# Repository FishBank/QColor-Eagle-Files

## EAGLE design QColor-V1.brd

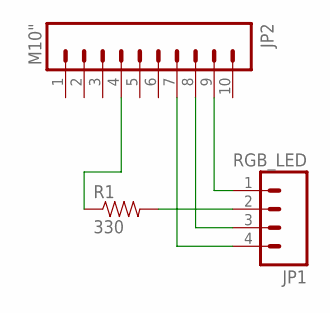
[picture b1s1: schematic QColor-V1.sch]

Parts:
JP1: RGB_LED; 1X04
JP2: M10"; 1X10
R1: 330; AXIAL-0.3

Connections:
unnamed: JP2.4, R1.P$1 (1)
unnamed: JP1.2, R1.P$2 (2)
unnamed: JP1.1, JP2.9
unnamed: JP1.3, JP2.8
unnamed: JP1.4, JP2.7

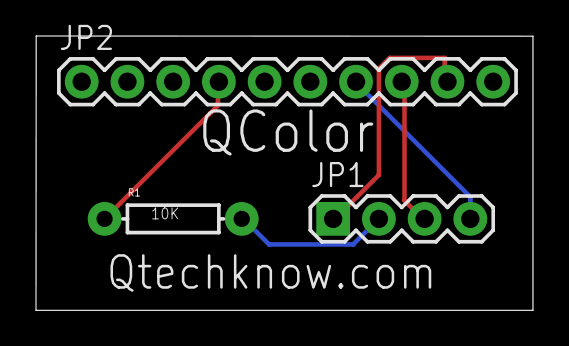
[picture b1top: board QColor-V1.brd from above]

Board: 2 copper layers, 27.6 x 15.2 mm, 3 parts (0 on the bottom side), 5 nets.

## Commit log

2012-07-13 Schematic

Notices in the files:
parts and their libraries:
SFE Connectors: Licensing: CC v3.0 Share-Alike You are welcome to use this library for commercial purposes.
